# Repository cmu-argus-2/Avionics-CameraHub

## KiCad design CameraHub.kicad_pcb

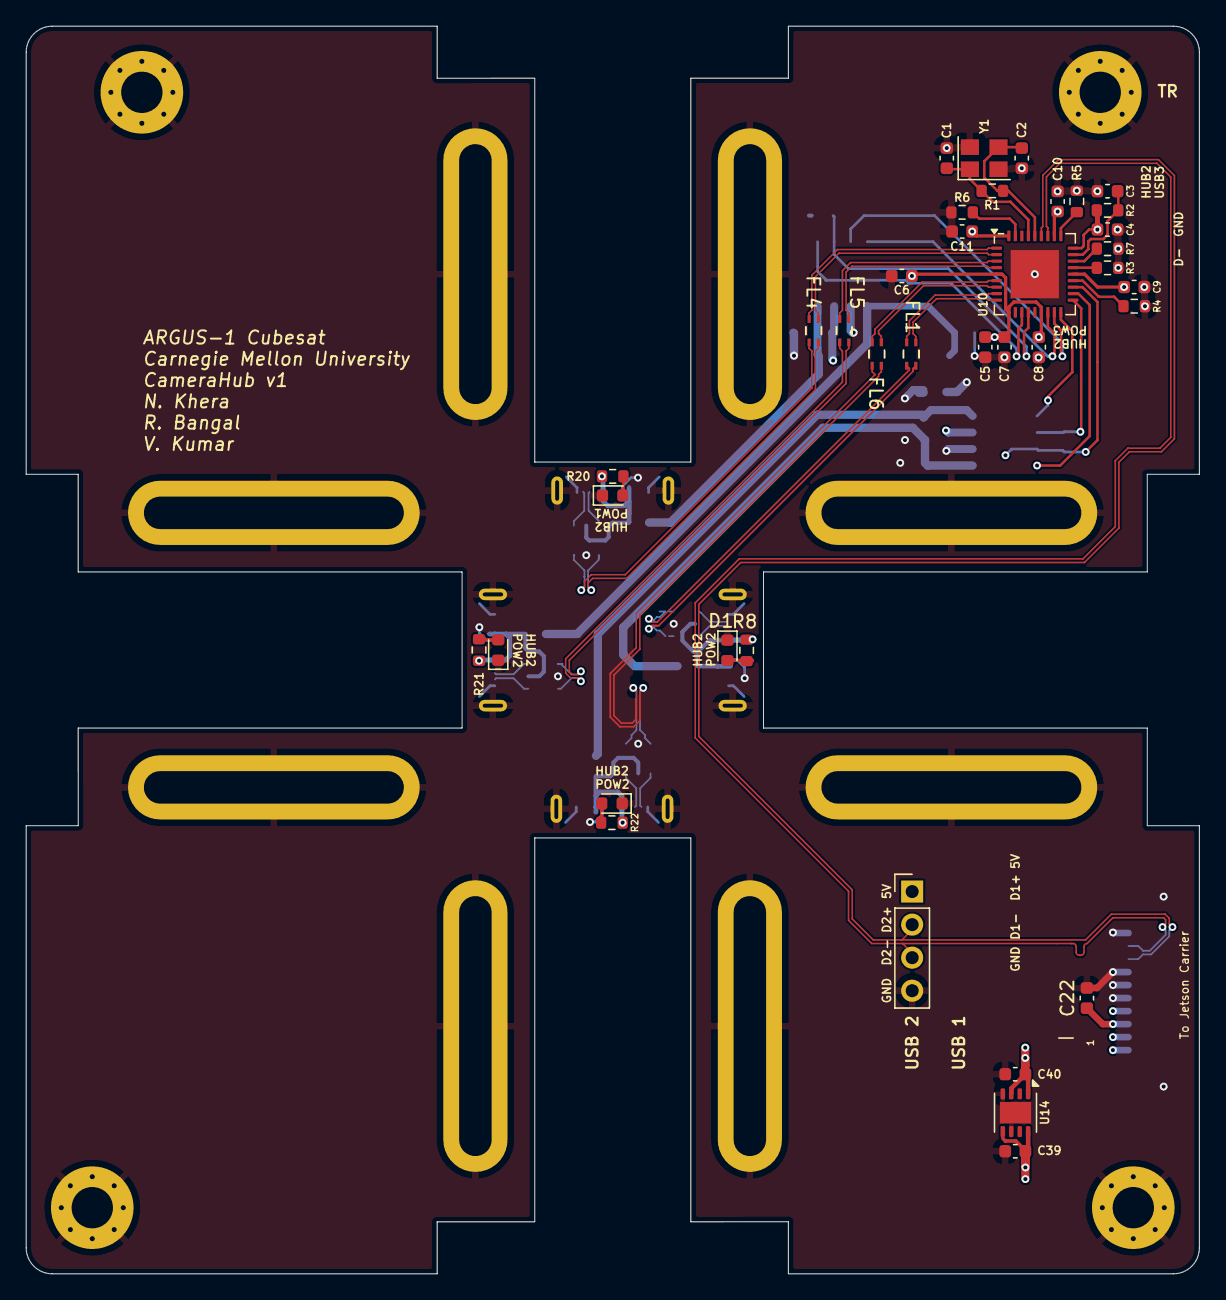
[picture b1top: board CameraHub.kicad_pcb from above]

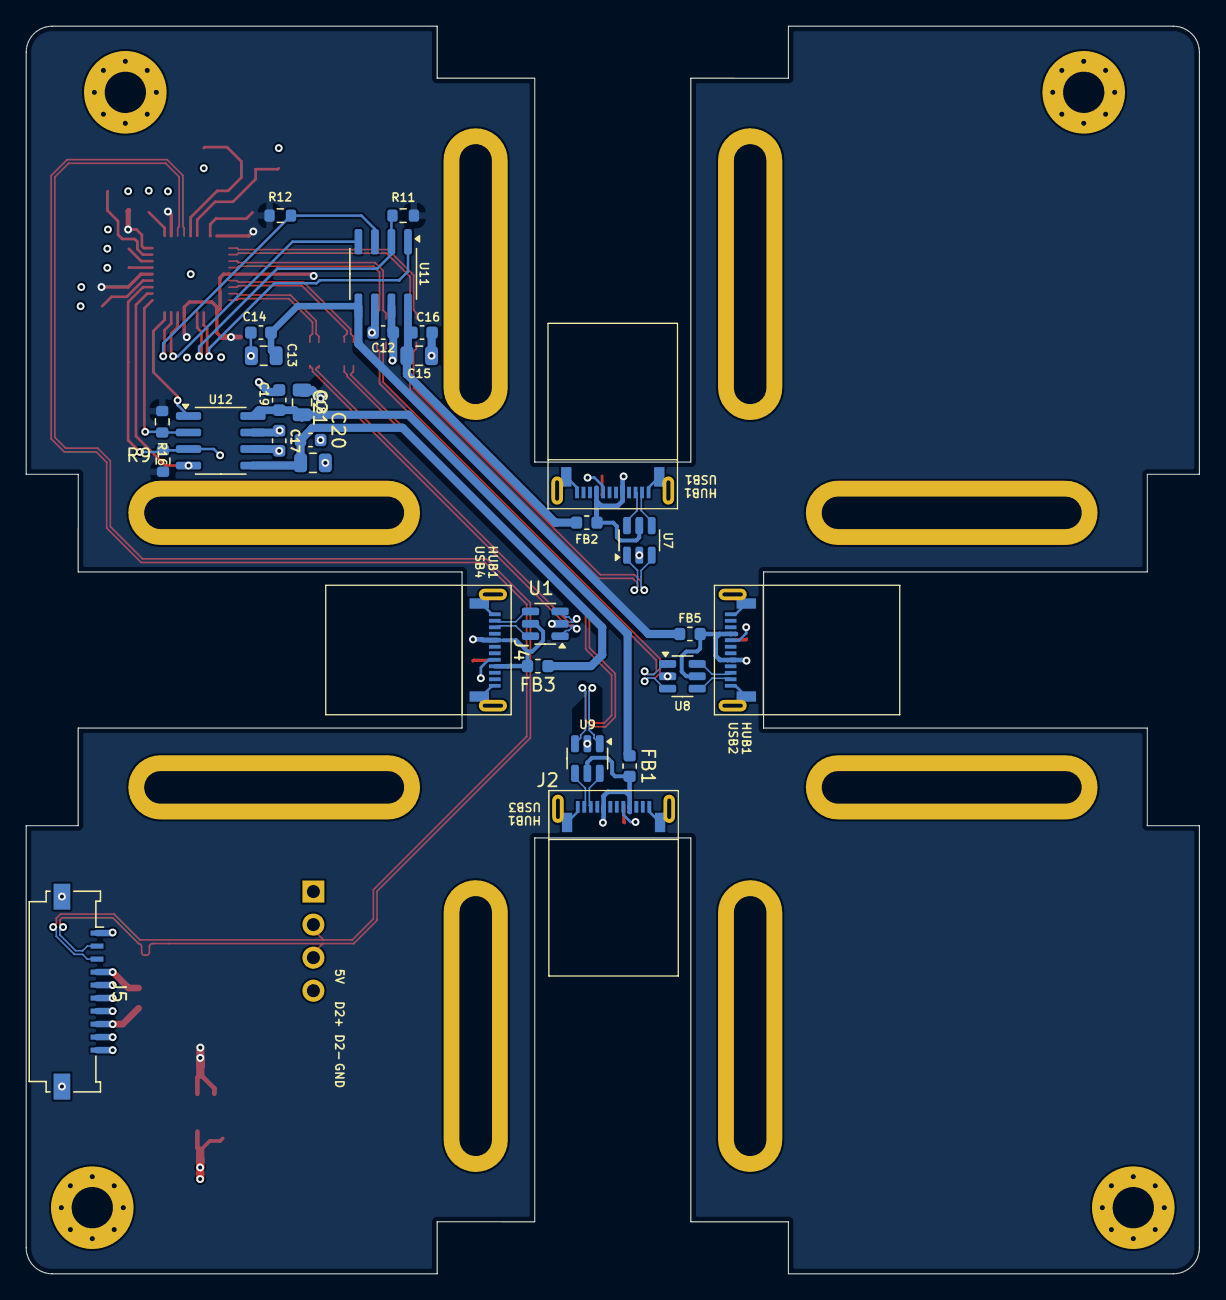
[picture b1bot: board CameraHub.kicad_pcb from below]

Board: 4 copper layers, 90.2 x 95.9 mm, 78 parts (33 on the bottom side), 57 nets.

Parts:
C1, C2: 27pF; C_0603_1608Metric
C3, C6, C7, C8, C9, C10, C11, C12, C14, C16, C17, C19, C21: 0.1uF; C_0603_1608Metric
C4: 4.7uF; C_0603_1608Metric
C5, C22, C39: 1uF; C_0603_1608Metric
C13, C15, C18, C20: 100uF; C_0805_2012Metric
C40: 22uF; C_0603_1608Metric
D1, D4, D5, D6: Green; LED_0603_1608Metric
FB1, FB2, FB3, FB5: 600R; L_0603_1608Metric
FL1, FL4, FL5, FL6: 744230900; CHIP_230900_WRE
H1, H2, H3, H4: MountingHole_Pad; MountingHole2
H5, H6, H7, H8, H9, H10, H11, H12: MountingHole_Pad; MountingHole_USB
J2, J4, J7, J8: USB_C_Receptacle_USB2.0_16P; USBC-121SMT-4BS2S
J3: Header 01x04 0.1"; PinHeader_1x04_P2.54mm_Vertical
J5: 200528-0100; Molex_200528-0100_1x10-1MP_P1.00mm_Horizontal
R1: 1M; R_0603_1608Metric
R2: 100K; R_0603_1608Metric
R3, R4, R5, R7: 36K; R_0603_1608Metric
R6: 12K; R_0603_1608Metric
R8, R20, R21, R22: 330R; R_0603_1608Metric
R9, R11, R12, R16: 10K; R_0603_1608Metric
U1, U7, U8, U9: USBLC6-2P6; SOT-23-6
U10: USB2514B-I/M2; QFN-36-1EP_6x6mm_P0.5mm_EP3.7x3.7mm
U11, U12: MIC2026-1xM; SOIC-8_3.9x4.9mm_P1.27mm
U14: TLV76733QWDRBxQ1; VSON-8-1EP_3x3mm_P0.65mm_EP1.65x2.4mm
Y1: 24MHz; Crystal_SMD_3225-4Pin_3.2x2.5mm

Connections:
+3.3V: C4.1, C5.1, C6.1, C7.1, C8.1, C9.1, C10.1, C11.1, C40.1, R2.2, R9.1, R11.1, R12.1, R16.1, U10.5 (VDDA33), U10.10 (VDDA33), U10.15 (VDD33), U10.23 (VDD33), U10.27 (VBUS_DET), U10.29 (VDDA33), U10.36 (VDDA33), U14.1 (OUT), U14.3 (SNS)
+5V: C12.1, C17.1, C22.2, C39.1, J3.1, J5.7, J5.8, J5.9, J5.10, U11.7 (IN), U12.7 (IN), U14.5 (EN), U14.8 (IN)
/Hub 2/D1_N: J7.A7 (D-), U7.4 (I/O2)
/Hub 2/D1_P: J7.A6 (D+), U7.6 (I/O1)
/Hub 2/D2_N: J8.A7 (D-), U8.4 (I/O2)
/Hub 2/D2_P: J8.A6 (D+), U8.6 (I/O1)
/Hub 2/D3_N: J2.A7 (D-), U9.4 (I/O2)
/Hub 2/D3_P: J2.A6 (D+), U9.6 (I/O1)
/Hub 2/D4_N: J4.A7 (D-), U1.4 (I/O2)
/Hub 2/D4_P: J4.A6 (D+), U1.6 (I/O1)
/Hub 2/FD1_N: FL4.3, U7.3 (I/O2)
/Hub 2/FD1_P: FL4.2, U7.1 (I/O1)
/Hub 2/FD2_N: FL5.3, U8.3 (I/O2)
/Hub 2/FD2_P: FL5.2, U8.1 (I/O1)
/Hub 2/FD3_N: FL6.3, U9.3 (I/O2)
/Hub 2/FD3_P: FL6.2, U9.1 (I/O1)
/Hub 2/FD4_N: FL1.3, U1.3 (I/O2)
/Hub 2/FD4_P: FL1.2, U1.1 (I/O1)
/Hub 2/HD1_N: FL4.4, U10.1 (USBDM_DN1/PRT_DIS_M1)
/Hub 2/HD1_P: FL4.1, U10.2 (USBDP_DN1/PRT_DIS_P1)
/Hub 2/HD2_N: FL5.4, U10.3 (USBDM_DN2/PRT_DIS_M2)
/Hub 2/HD2_P: FL5.1, U10.4 (USBDP_DN2/PRT_DIS_P2)
/Hub 2/HD3_N: FL6.4, U10.6 (USBDM_DN3/PRT_DIS_M3)
/Hub 2/HD3_P: FL6.1, U10.7 (USBDP_DN3/PRT_DIS_P3)
/Hub 2/HD4_N: FL1.4, U10.8 (USBDM_DN4/PRT_DIS_M4)
/Hub 2/HD4_P: FL1.1, U10.9 (USBDP_DN4/PRT_DIS_P4)
/Hub 2/PWR1: U10.12 (PRTPWR1/BC_EN1), U11.1 (ENA)
/Hub 2/PWR2: U10.16 (PRTPWR2/BC_EN2), U11.4 (ENB)
/Hub 2/PWR3: U10.18 (PRTPWR3/BC_EN3), U12.1 (ENA)
/Hub 2/PWR4: U10.20 (PRTPWR4/BC_EN4), U12.4 (ENB)
/Hub 2/VBUS1: C15.1, C16.1, FB2.1, U11.8 (OUTA)
/Hub 2/VBUS2: C13.1, C14.1, FB5.1, U11.5 (OUTB)
/Hub 2/VBUS3: C18.1, C19.1, FB1.1, U12.8 (OUTA)
/Hub 2/VBUS4: C20.1, C21.1, FB3.1, U12.5 (OUTB)
/Hub 2/VBUS_CONN1: FB2.2, J7.A4 (VBUS), J7.B9 (VBUS), R20.1, U7.5 (VBUS)
/Hub 2/VBUS_CONN2: FB5.2, J8.A4 (VBUS), J8.B9 (VBUS), R21.1, U8.5 (VBUS)
/Hub 2/VBUS_CONN3: FB1.2, J2.A4 (VBUS), J2.B9 (VBUS), R22.1, U9.5 (VBUS)
/Hub 2/VBUS_CONN4: FB3.2, J4.A4 (VBUS), J4.B9 (VBUS), R8.1, U1.5 (VBUS)
/Hub 2/nOCS1: R11.2, U10.13 (OCS_N1), U11.2 (FLGA)
/Hub 2/nOCS2: R12.2, U10.17 (OCS_N2), U11.3 (FLGB)
/Hub 2/nOCS3: R16.2, U10.19 (OCS_N3), U12.2 (FLGA)
/Hub 2/nOCS4: R9.2, U10.21 (OCS_N4), U12.3 (FLGB)
/USB_N: J3.3, J5.2, U10.30 (USBDM_UP)
/USB_P: J3.2, J5.3, U10.31 (USBDP_UP)
/nRST: C3.1, R2.1, U10.26 (RESET_N)
GND: C1.2, C2.2, C3.2, C4.2, C5.2, C6.2, C7.2, C8.2, C9.2, C10.2, C11.2, C12.2, C13.2, C14.2, C15.2, C16.2, C17.2, C18.2, C19.2, C20.2, C21.2, C22.1, C39.2, C40.2, D1.1 (K), D4.1 (K), D5.1 (K), D6.1 (K), H1.1, H2.1, H3.1, H4.1, H5.1, H6.1, H7.1, H8.1, H9.1, H10.1, H11.1, H12.1, J2.A1 (GND), J2.A12 (GND), J2.B12 (GND), J2.S1 (SHIELD), J3.4, J4.A1 (GND), J4.A12 (GND), J4.B12 (GND), J4.S1 (SHIELD), J5.1, J5.4, J5.5, J5.6, J5.MP (MountPin), J7.A1 (GND), J7.A12 (GND), J7.B12 (GND), J7.S1 (SHIELD), J8.A1 (GND), J8.A12 (GND), J8.B12 (GND), J8.S1 (SHIELD), R3.2, R4.2, R5.2, R6.1, R7.2, U1.2 (GND), U7.2 (GND), U8.2 (GND), U9.2 (GND), U10.37 (VSS), U11.6 (GND), U12.6 (GND), U14.4 (GND), U14.6 (GND), U14.9 (PAD), Y1.2, Y1.4
unnamed: D1.2 (A), R8.2
unnamed: D4.2 (A), R20.2
unnamed: D5.2 (A), R21.2
unnamed: D6.2 (A), R22.2
unnamed: R7.1, U10.25 (HS_IND/CFG_SEL1)
unnamed: R6.2, U10.35 (RBIAS)
unnamed: R3.1, U10.24 (SCL/SMBCLK/CFG_SEL0)
unnamed: R4.1, U10.22 (SDA/SMBDATA/NON_REM1)
unnamed: R5.1, U10.28 (SUSP_IND/LOCAL_PWR/NON_REM0)
unnamed: C1.1, R1.1, U10.33 (XTALIN/CLKIN), Y1.1
unnamed: C2.1, R1.2, U10.32 (XTALOUT), Y1.3

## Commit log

2024-06-22 Upload .gitignore
2024-06-22 Upload v1 Project Files
2024-06-28 Complete layout
2024-07-02 Budged Jetson FPC connector
2024-07-19 v1 Final
2024-11-01 Finished Camera Hub
2024-11-06 rev2.1
2024-11-11 rev2?'
2024-11-18 BOM added

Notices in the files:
parts and their libraries:
License: Apache-2.0
